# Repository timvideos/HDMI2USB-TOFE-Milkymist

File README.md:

## Milkymist Compatibility - TOFE Expansion board

The [Numato Opsis board](https://numato.com/product/numato-opsis-fpga-based-open-video-platform) is
already very similar to the [Milkymist M1](http://m-labs.hk/m1.html) and
[Mixxeo](http://m-labs.hk/mixxeo.html) devices created by
[M-Labs](http://m-labs.hk/), but lacks the DJ hardware interfaces. This
expansion board adds these missing components.

This board can be ordered from the
[Numato Opsis page on CrowdSupply.com](https://www.crowdsupply.com/numato-lab/opsis).

## Features

This extension board has the following features;

 * [AC‘97 compatible](https://en.wikipedia.org/wiki/AC%2797)
   audio interface with Microphone, Headphones, Line In + Out (on standard
   3.5mm connectors).

 * [RS-422](https://en.wikipedia.org/wiki/RS-422) / [RS-485](https://en.wikipedia.org/wiki/RS-485)
   compatible high speed (10Mbps), full duplex serial port;

    * Compatible with wide range of interfaces including the industry standard
      [DMX512 control protocol](https://en.wikipedia.org/wiki/DMX512).

    * Connected to screw terminal headers, allowing wiring to DB-9, RJ-12,
      XLR-5, XLR-3 or RJ-45 connectors (wiring diagrams provided).

 * [RS-232](https://en.wikipedia.org/wiki/RS-232) full duplex serial port on a
   standard DB-9 connector. Supporting connection to wide range of devices with
   serial ports. (A secondary RS-232 full duplex serial port on a standard
   screw terminal.)

 * [MIDI](https://en.wikipedia.org/wiki/MIDI) In and Out interfaces on screw
   terminals, supporting connection to wide range of musical instruments and
   control devices.

 * [Infrared](https://learn.adafruit.com/ir-sensor/ir-remote-signals)
   transmitter and receiver compatible with manys
   [consumer remote protocols](https://en.wikipedia.org/wiki/Consumer_IR).

 * 4 x Push button Switches,
 * 4 x Indicator LEDs,

 * 2 x [Digilent Pmod™ Compatible](http://www.digilentinc.com/Pmods/licensing.cfm)
   headers to allow usage of existing expansion boards, including boards froms
   [Numato Lab](http://numato.com/fpga-boards/filter/cat/expansion-modules.html?limit=30),
   [Digilent](http://digilentinc.com/pmods),
   [Maxim](https://www.maximintegrated.com/en/design/design-technology/fpga-design-resources/pmod-compatible-plug-in-peripheral-modules.html) ands
   [Analog](https://wiki.analog.com/resources/alliances/xilinx#pmods).

A PDF version of the schematic can be found in the [docs](docs) directory.

## Editing

The design in this repository was made using [KiCad](http://www.kicad-pcb.org/)
version **2013-07-07 BZR 4022**
([the version is Ubuntu Trusty](http://packages.ubuntu.com/trusty/kicad)).

## License

TOFE MilkyMist Compatibility Expansion board by Numato Systems Pvt. Ltd

TOFE MilkyMist Compatibility Expansion board is licensed under a
Creative Commons Attribution-ShareAlike 4.0 International License.

You should have received a copy of the license along with this
work. If not, see <http://creativecommons.org/licenses/by-sa/4.0/>.

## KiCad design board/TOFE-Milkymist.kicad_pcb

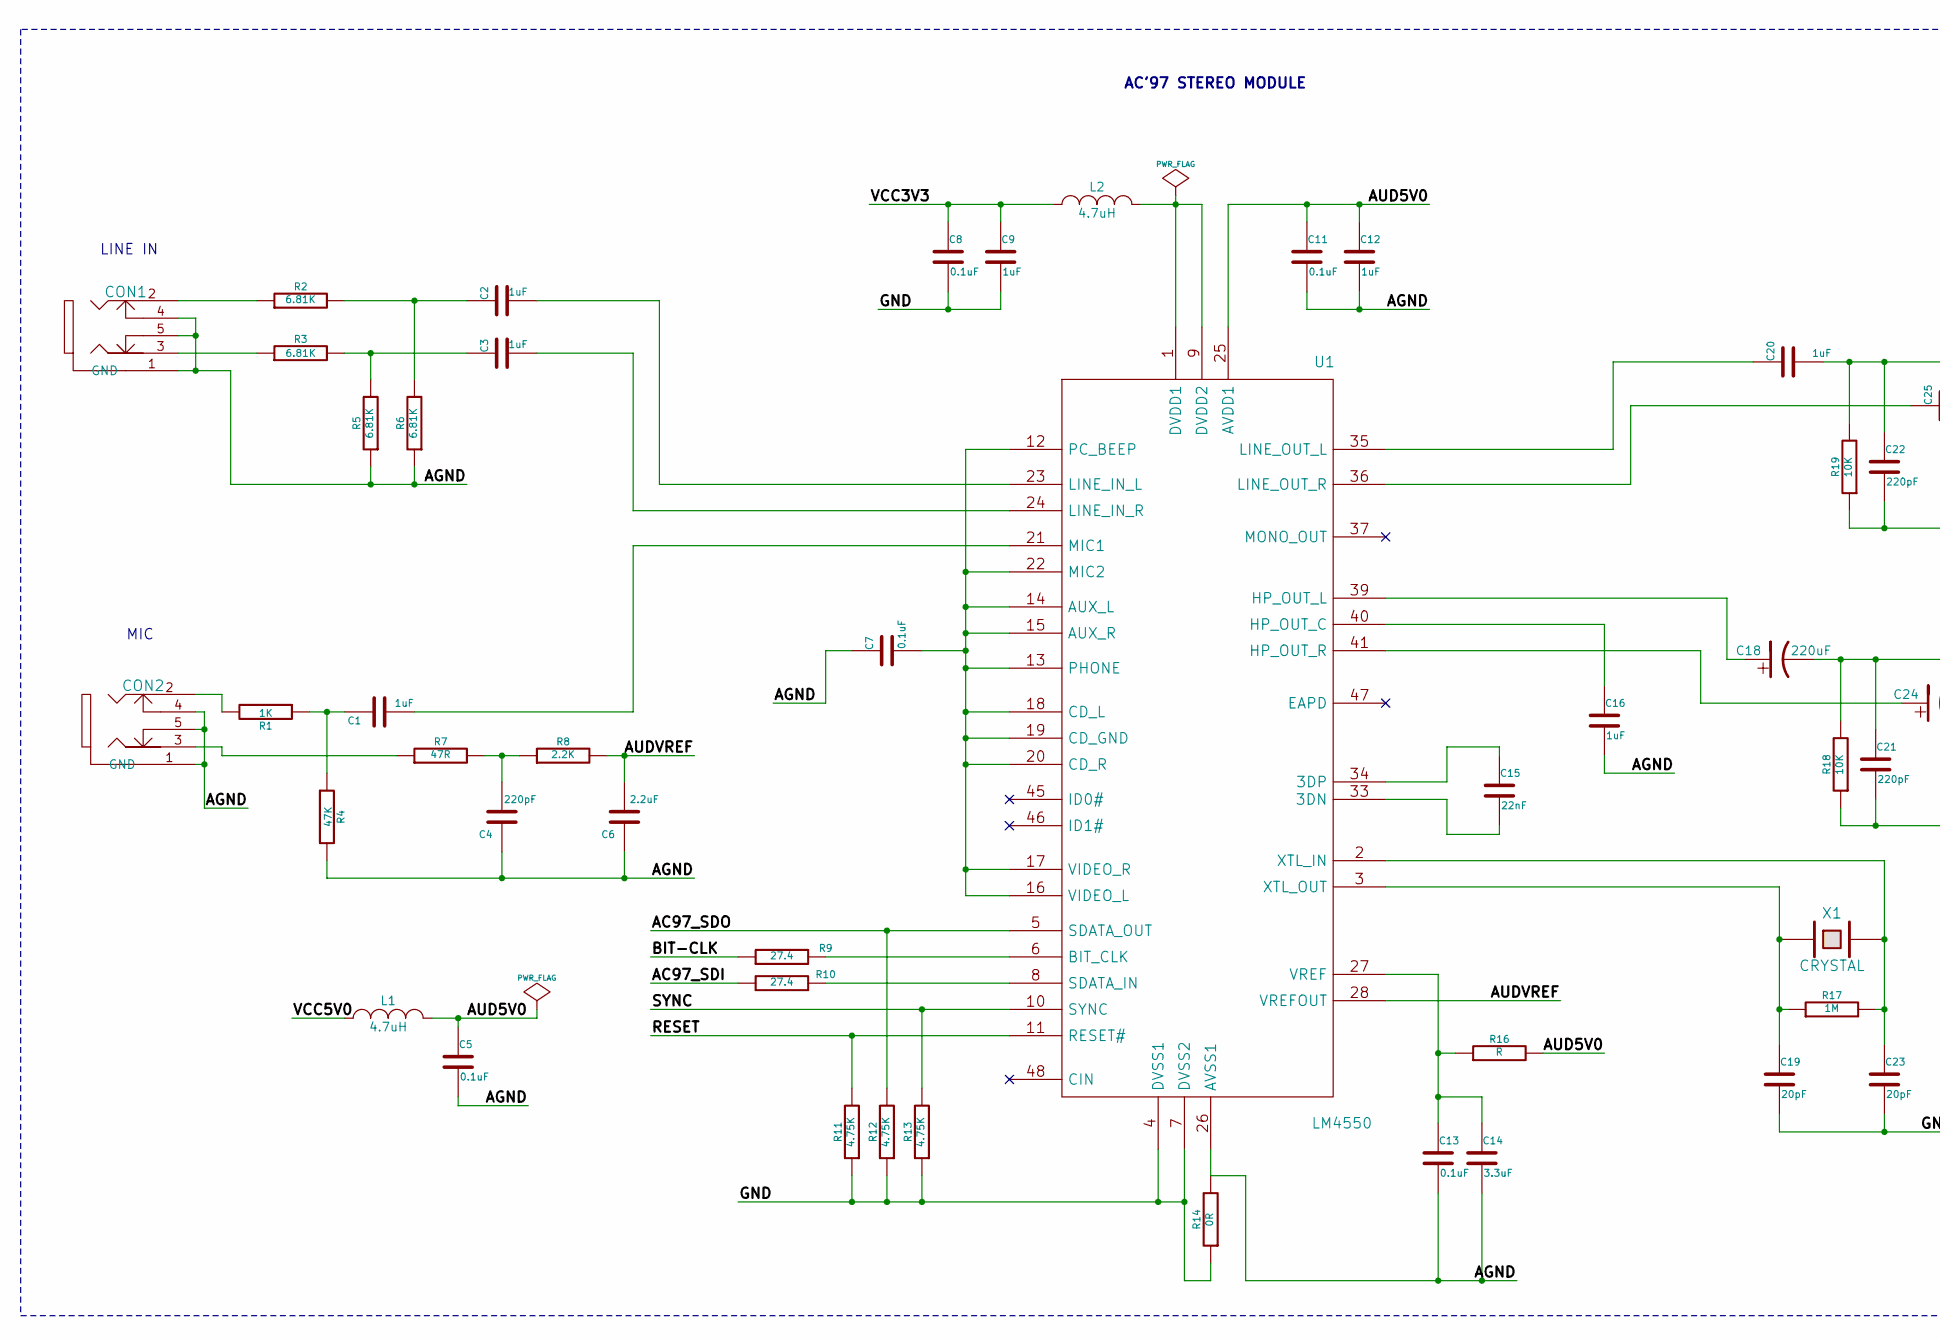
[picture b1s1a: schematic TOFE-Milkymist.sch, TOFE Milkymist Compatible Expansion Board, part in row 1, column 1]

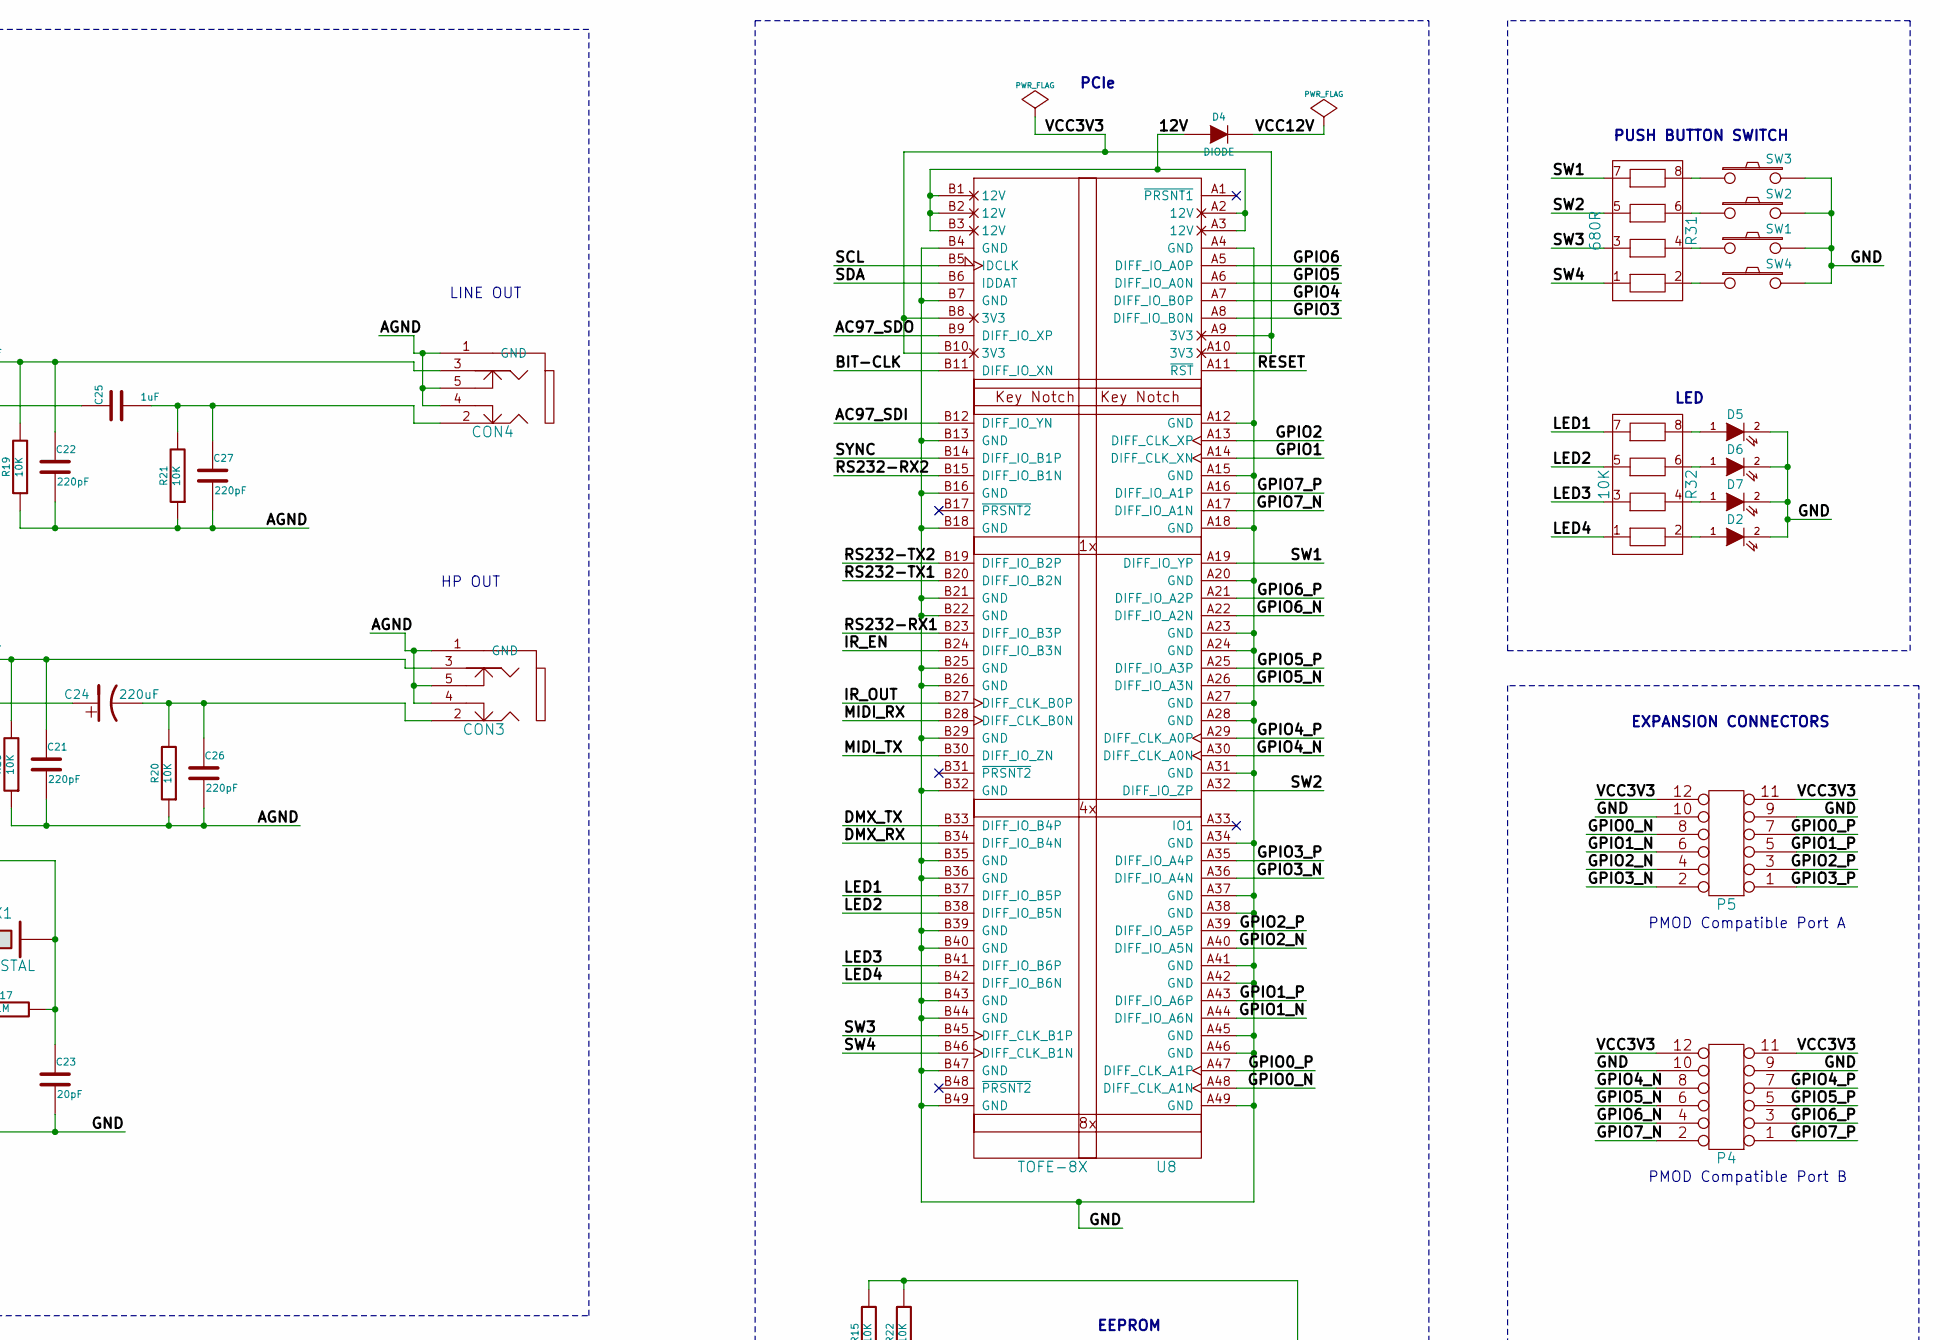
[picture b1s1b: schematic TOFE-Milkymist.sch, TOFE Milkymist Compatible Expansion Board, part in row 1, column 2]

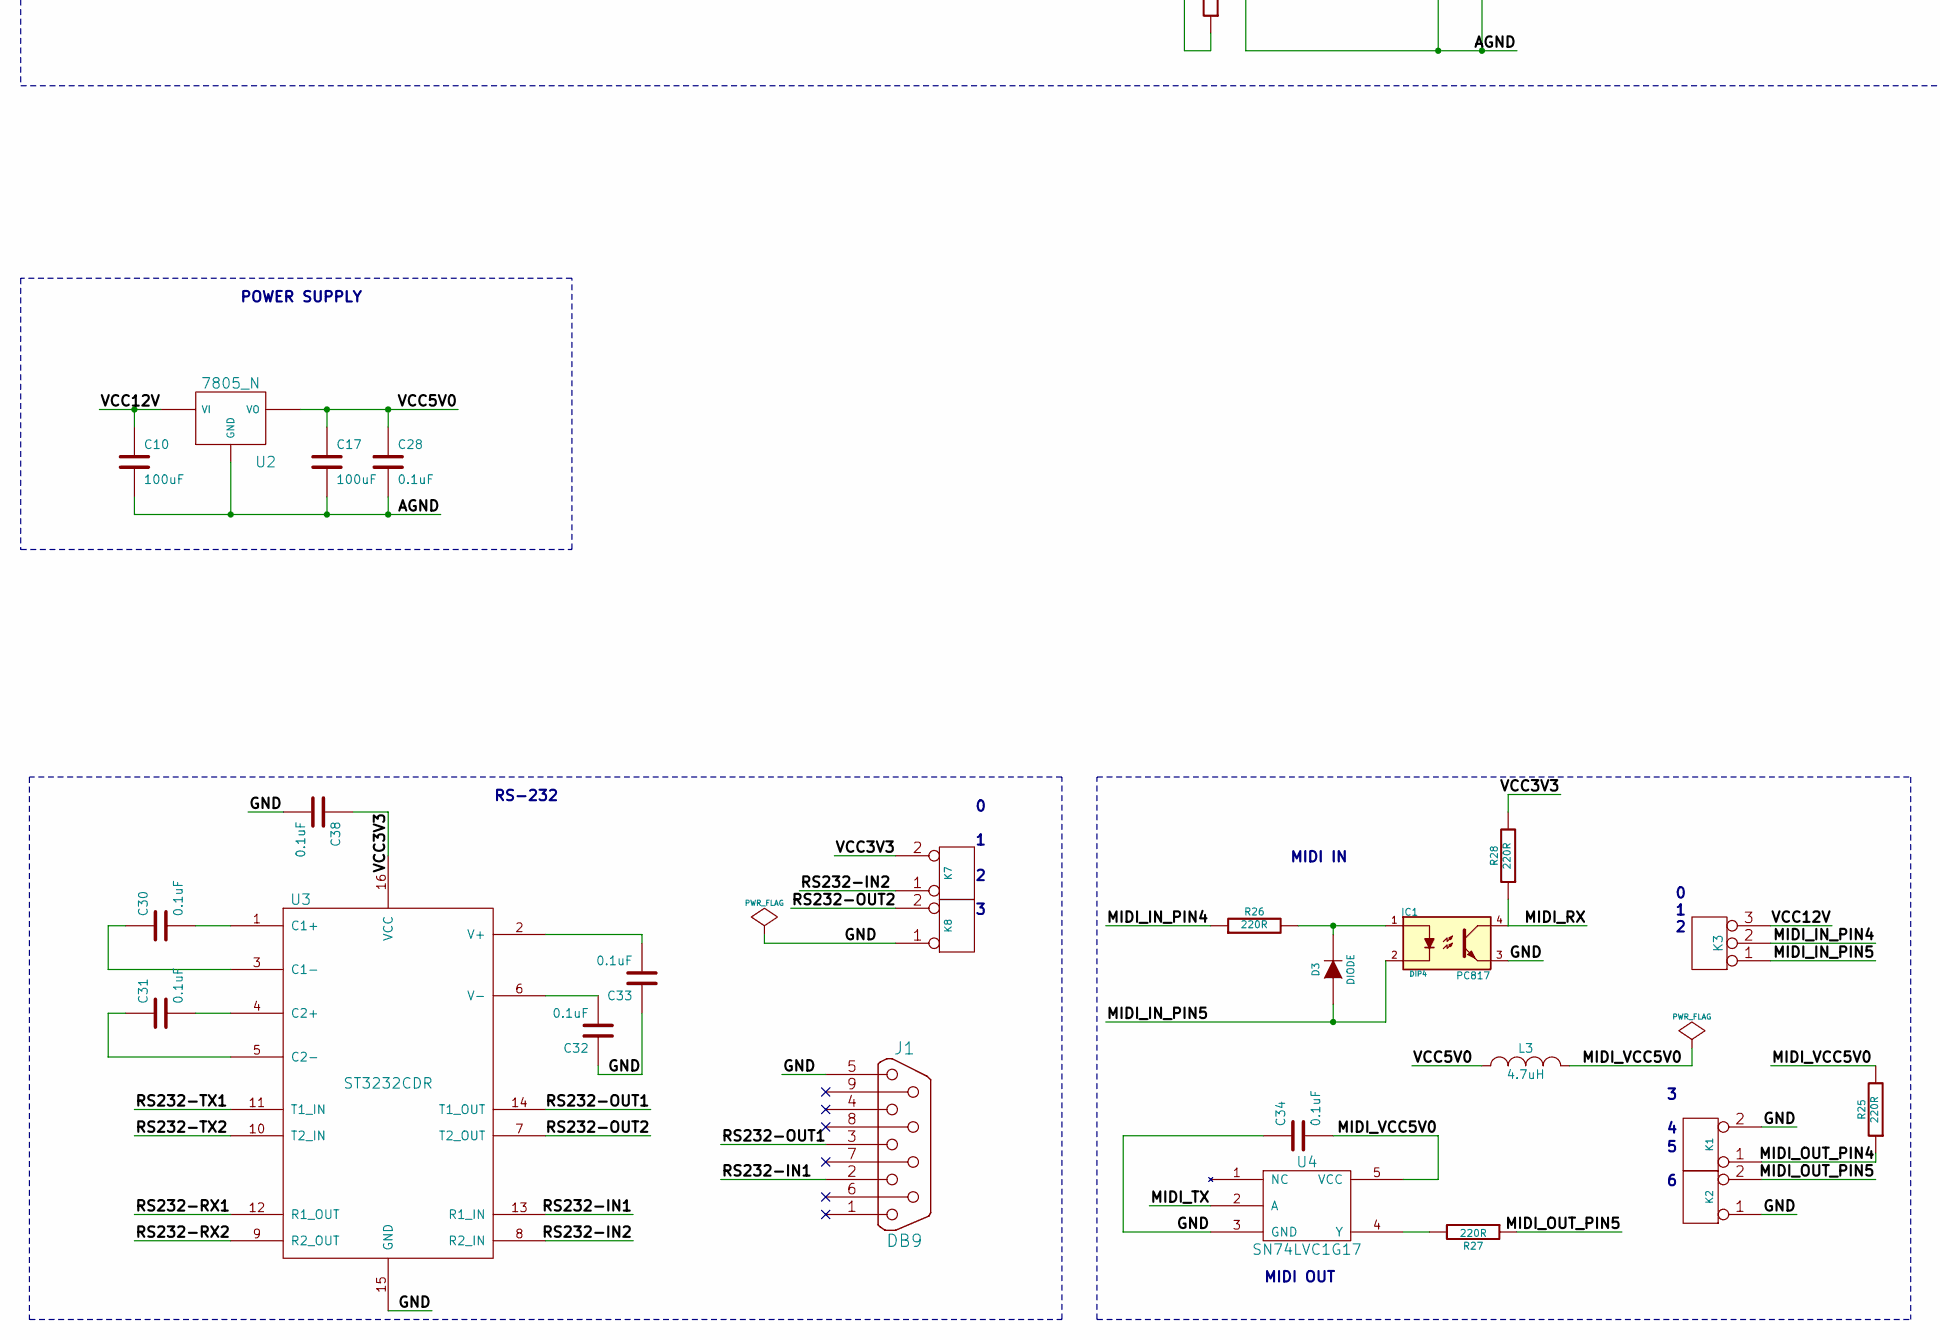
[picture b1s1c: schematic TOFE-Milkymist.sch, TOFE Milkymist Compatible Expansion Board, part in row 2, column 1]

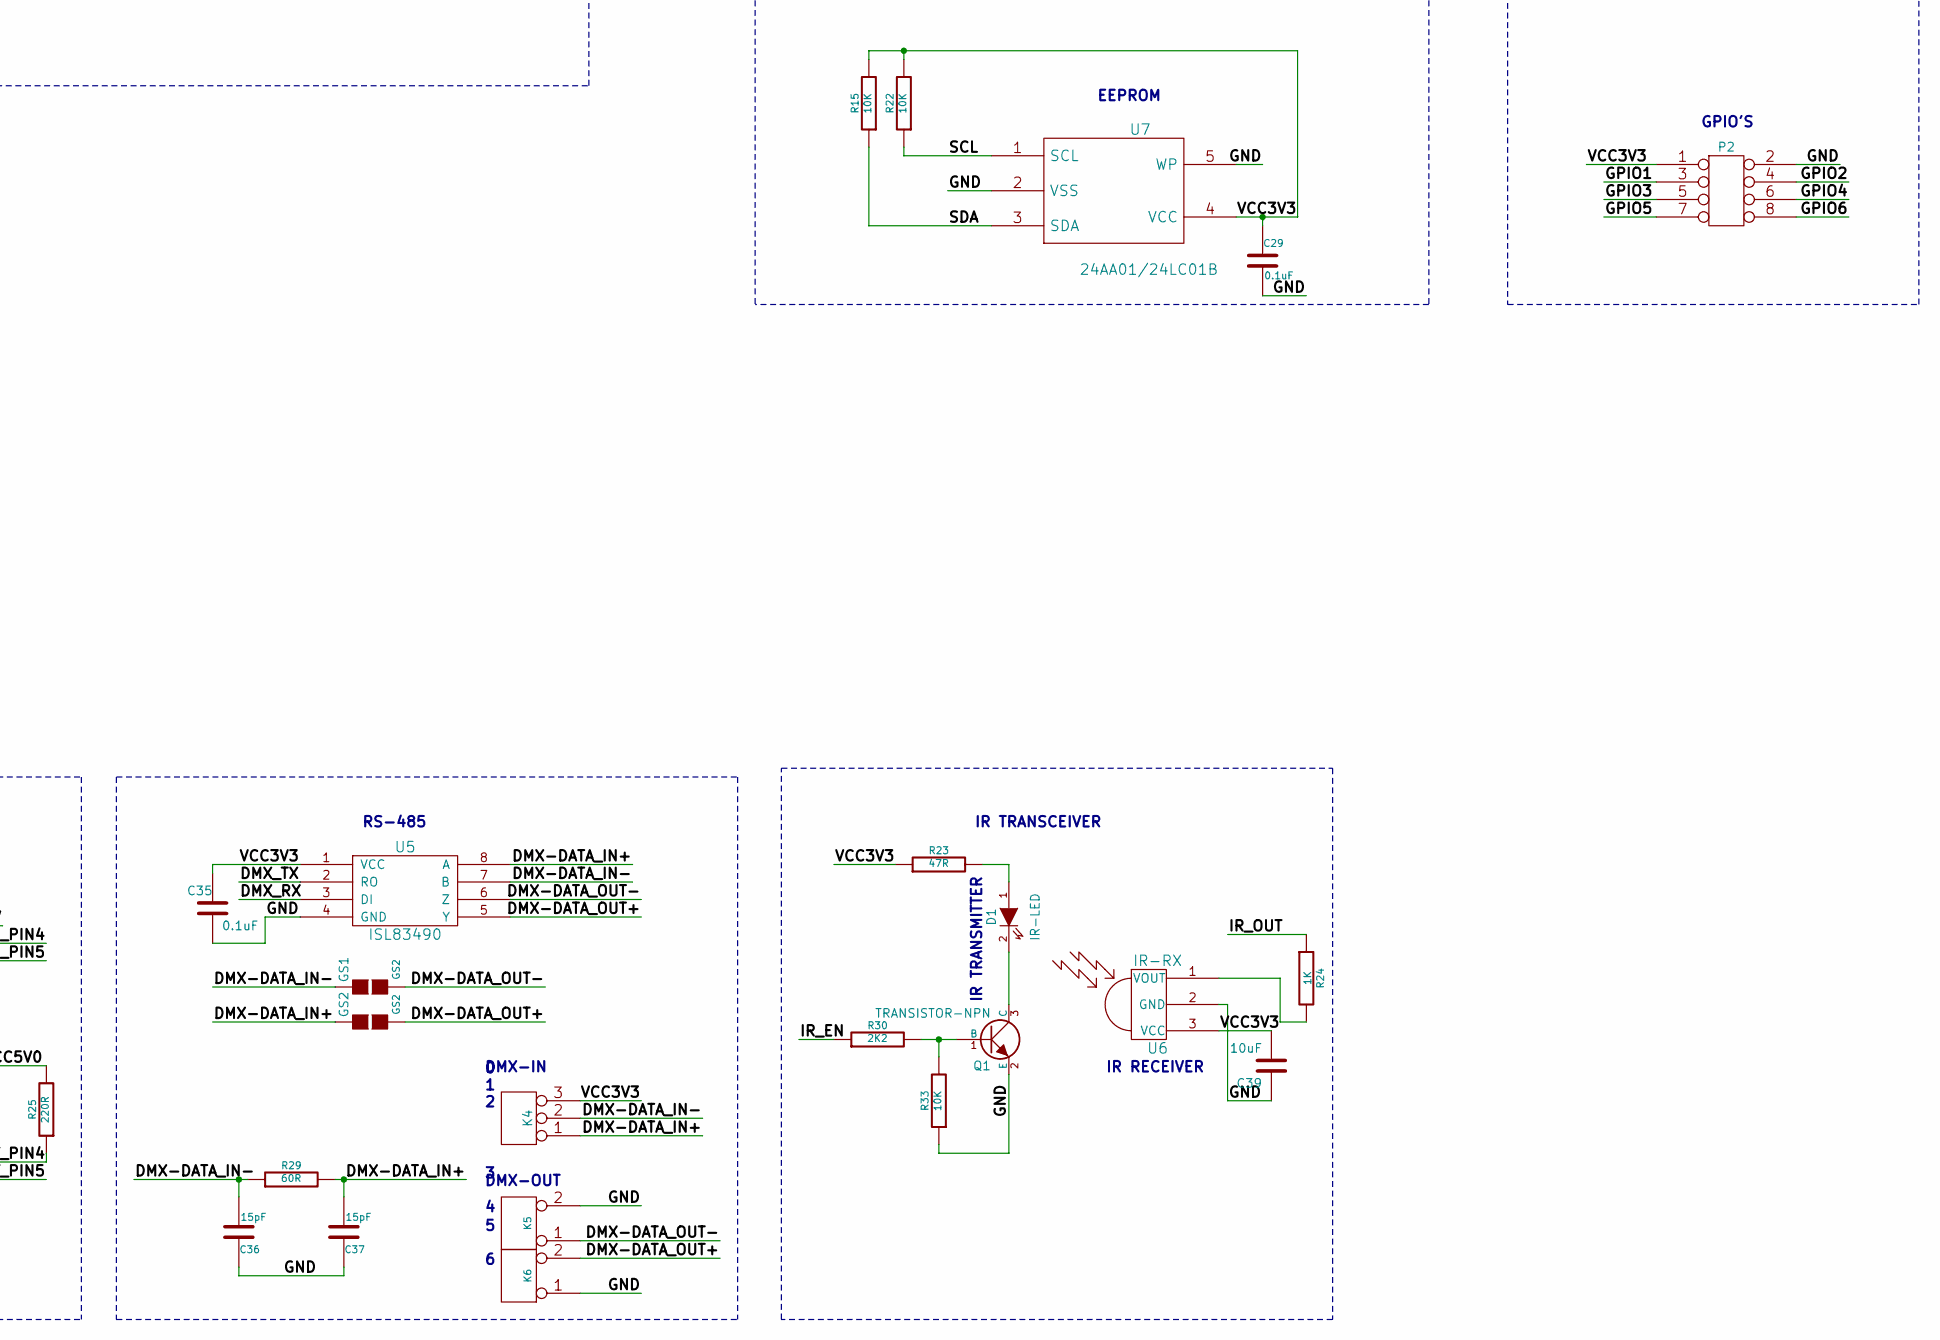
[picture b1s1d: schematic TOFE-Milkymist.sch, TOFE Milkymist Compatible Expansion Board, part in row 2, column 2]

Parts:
C1, C2, C3, C9, C12, C16, C20, C25: 1uF
C4, C21, C22, C26, C27: 220pF
C5, C7, C8, C11, C13, C28, C29, C30, C31, C32, C33, C34, C35, C38: 0.1uF
C6: 2.2uF
C10, C17: 100uF
C14: 3.3uF
C15: 22nF
C18, C24: 220uF
C19, C23: 20pF
C36, C37: 15pF
C39: 10uF
CON1, CON2, CON3, CON4: AUDIO_JACK_3535NG
D1: IR-LED
D2, D5, D6, D7: LED
D3, D4: DIODE
GS1, GS2: GS2
IC1: PC817; DIP4
J1: DB9
K1, K2, K5, K6, K7, K8: CONN_2
K3, K4: CONN_3
L1, L2, L3: 4.7uH
P2: CONN_4X2
P4, P5: CONN_6X2
Q1: TRANSISTOR-NPN
R1, R24: 1K
R2, R3, R5, R6: 6.81K
R4: 47K
R7, R23: 47R
R8: 2.2K
R9, R10: 27.4
R11, R12, R13: 4.75K
R14: 0R
R15, R18, R19, R20, R21, R22, R32, R33: 10K
R16: R
R17: 1M
R25, R26, R27, R28: 220R
R29: 60R
R30: 2K2
R31: 680R
SW1, SW2, SW3, SW4: SW_PUSH
U1: LM4550
U2: 7805_N
U3: ST3232CDR
U4: SN74LVC1G17
U5: ISL83490
U6: IR-RX
U7: 24AA01/24LC01B
U8: TOFE-8X
X1: CRYSTAL

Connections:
/12V: D4.1 (A), U8.A2 (12V), U8.A3 (12V), U8.B1 (12V), U8.B2 (12V), U8.B3 (12V)
/AC97_SDI: R10.1, U8.B12 (DIFF_IO_YN)
/AC97_SDO: R12.2, U1.5 (SDATA_OUT), U8.B9 (DIFF_IO_XP)
/AGND: C4.1, C5.2, C6.1, C7.1, C10.2, C11.2, C12.2, C13.2, C14.2, C16.2, C17.2, C21.2, C22.2, C26.2, C27.2, C28.2, CON1.1 (GND), CON1.4, CON1.5, CON2.1 (GND), CON2.4, CON2.5, CON3.1 (GND), CON3.4, CON3.5, CON4.1 (GND), CON4.4, CON4.5, R4.2, R5.1, R6.1, R14.2, R18.1, R19.1, R20.1, R21.1, U1.26 (AVSS1), U2.2 (GND)
/AUD5V0: C5.1, C11.1, C12.1, L1.2, R16.2, U1.25 (AVDD1)
/AUDVREF: C6.2, R8.2, U1.28 (VREFOUT)
/BIT-CLK: R9.1, U8.B11 (DIFF_IO_XN)
/DMX-DATA_IN+: C37.2, GS2.1 (G1), K4.1, R29.2, U5.8 (A)
/DMX-DATA_IN-: C36.2, GS1.1 (G1), K4.2 (PM), R29.1, U5.7 (B)
/DMX-DATA_OUT+: GS2.2 (G2), K6.2 (PM), U5.5 (Y)
/DMX-DATA_OUT-: GS1.2 (G2), K5.1, U5.6 (Z)
/DMX_RX: U5.3 (DI), U8.B34 (DIFF_IO_B4N)
/DMX_TX: U5.2 (RO), U8.B33 (DIFF_IO_B4P)
/GND: C8.2, C9.2, C19.2, C23.2, C29.2, C32.1, C33.1, C34.1, C35.2, C36.1, C37.1, C38.2, C39.1, D2.2 (K), D5.2 (K), D6.2 (K), D7.2 (K), IC1.3, J1.5, K1.2 (PM), K2.1, K5.2 (PM), K6.1, K8.1, P2.2, P4.9, P4.10, P5.9, P5.10, Q1.2 (E), R11.1, R12.1, R13.1, R14.1, R33.1, SW1.2, SW2.2, SW3.2, SW4.2, U1.4 (DVSS1), U1.7 (DVSS2), U3.15 (GND), U4.3 (GND), U5.4 (GND), U6.2 (GND), U7.2 (VSS), U7.5 (WP), U8.A4 (GND), U8.A12 (GND), U8.A15 (GND), U8.A18 (GND), U8.A20 (GND), U8.A23 (GND), U8.A24 (GND), U8.A27 (GND), U8.A28 (GND), U8.A31 (GND), U8.A34 (GND), U8.A37 (GND), U8.A38 (GND), U8.A41 (GND), U8.A42 (GND), U8.A45 (GND), U8.A46 (GND), U8.A49 (GND), U8.B4 (GND), U8.B7 (GND), U8.B13 (GND), U8.B16 (GND), U8.B18 (GND), U8.B21 (GND), U8.B22 (GND), U8.B25 (GND), U8.B26 (GND), U8.B29 (GND), U8.B32 (GND), U8.B35 (GND), U8.B36 (GND), U8.B39 (GND), U8.B40 (GND), U8.B43 (GND), U8.B44 (GND), U8.B47 (GND), U8.B49 (GND)
/GPIO0_N: P5.8, U8.A48 (DIFF_CLK_A1N)
/GPIO0_P: P5.7, U8.A47 (DIFF_CLK_A1P)
/GPIO1: P2.3, U8.A14 (DIFF_CLK_XN)
/GPIO1_N: P5.6, U8.A44 (DIFF_IO_A6N)
/GPIO1_P: P5.5, U8.A43 (DIFF_IO_A6P)
/GPIO2: P2.4, U8.A13 (DIFF_CLK_XP)
/GPIO2_N: P5.4, U8.A40 (DIFF_IO_A5N)
/GPIO2_P: P5.3, U8.A39 (DIFF_IO_A5P)
/GPIO3: P2.5, U8.A8 (DIFF_IO_B0N)
/GPIO3_N: P5.2, U8.A36 (DIFF_IO_A4N)
/GPIO3_P: P5.1, U8.A35 (DIFF_IO_A4P)
/GPIO4: P2.6, U8.A7 (DIFF_IO_B0P)
/GPIO4_N: P4.8, U8.A30 (DIFF_CLK_A0N)
/GPIO4_P: P4.7, U8.A29 (DIFF_CLK_A0P)
/GPIO5: P2.7, U8.A6 (DIFF_IO_A0N)
/GPIO5_N: P4.6, U8.A26 (DIFF_IO_A3N)
/GPIO5_P: P4.5, U8.A25 (DIFF_IO_A3P)
/GPIO6: P2.8, U8.A5 (DIFF_IO_A0P)
/GPIO6_N: P4.4, U8.A22 (DIFF_IO_A2N)
/GPIO6_P: P4.3, U8.A21 (DIFF_IO_A2P)
/GPIO7_N: P4.2, U8.A17 (DIFF_IO_A1N)
/GPIO7_P: P4.1, U8.A16 (DIFF_IO_A1P)
/IR_EN: R30.1, U8.B24 (DIFF_IO_B3N)
/IR_OUT: R24.1, U8.B27 (DIFF_CLK_B0P)
/LED1: R32.7, U8.B37 (DIFF_IO_B5P)
/LED2: R32.5, U8.B38 (DIFF_IO_B5N)
/LED3: R32.3, U8.B41 (DIFF_IO_B6P)
/LED4: R32.1, U8.B42 (DIFF_IO_B6N)
/MIDI_IN_PIN4: K3.2 (PM), R26.1
/MIDI_IN_PIN5: D3.1 (A), IC1.2, K3.1
/MIDI_OUT_PIN4: K1.1, R25.1
/MIDI_OUT_PIN5: K2.2 (PM), R27.1
/MIDI_RX: IC1.4, R28.1, U8.B28 (DIFF_CLK_B0N)
/MIDI_TX: U4.2 (A), U8.B30 (DIFF_IO_ZN)
/MIDI_VCC5V0: C34.2, L3.2, R25.2, U4.5 (VCC)
/RESET: R11.2, U1.11 (RESET#), U8.A11 (~RST)
/RS232-IN1: J1.2, U3.13 (R1_IN)
/RS232-IN2: K7.1, U3.8 (R2_IN)
/RS232-OUT1: J1.3, U3.14 (T1_OUT)
/RS232-OUT2: K8.2 (PM), U3.7 (T2_OUT)
/RS232-RX1: U3.12 (R1_OUT), U8.B23 (DIFF_IO_B3P)
/RS232-RX2: U3.9 (R2_OUT), U8.B15 (DIFF_IO_B1N)
/RS232-TX1: U3.11 (T1_IN), U8.B20 (DIFF_IO_B2N)
/RS232-TX2: U3.10 (T2_IN), U8.B19 (DIFF_IO_B2P)
/SCL: R22.1, U7.1 (SCL), U8.B5 (IDCLK)
/SDA: R15.1, U7.3 (SDA), U8.B6 (IDDAT)
/SW1: R31.7, U8.A19 (DIFF_IO_YP)
/SW2: R31.5, U8.A32 (DIFF_IO_ZP)
/SW3: R31.3, U8.B45 (DIFF_CLK_B1P)
/SW4: R31.1, U8.B46 (DIFF_CLK_B1N)
/SYNC: R13.2, U1.10 (SYNC), U8.B14 (DIFF_IO_B1P)
/VCC3V3: C8.1, C9.1, C29.1, C35.1, C38.1, C39.2, K4.3, K7.2 (PM), L2.1, P2.1, P4.11, P4.12, P5.11, P5.12, R15.2, R22.2, R23.1, R28.2, U3.16 (VCC), U5.1 (VCC), U6.3 (VCC), U7.4 (VCC), U8.A9 (3V3), U8.A10 (3V3), U8.B8 (3V3), U8.B10 (3V3)
/VCC5V0: C17.1, C28.1, L1.1, L3.1, U2.3 (VO)
/VCC12V: C10.1, D4.2 (K), K3.3, U2.1 (VI)
unnamed: CON2.3, R7.1
unnamed: CON2.2, R1.2
unnamed: C3.2, U1.24 (LINE_IN_R)
unnamed: C2.2, U1.23 (LINE_IN_L)
unnamed: C13.1, C14.1, R16.1, U1.27 (VREF)
unnamed: C18.2, C21.1, CON3.3, R18.2
unnamed: C24.1, U1.41 (HP_OUT_R)
unnamed: C15.2, U1.33 (3DN)
unnamed: C15.1, U1.34 (3DP)
unnamed: R10.2, U1.8 (SDATA_IN)
unnamed: R9.2, U1.6 (BIT_CLK)
unnamed: C1.1, R1.1, R4.1
unnamed: C20.1, U1.35 (LINE_OUT_L)
unnamed: C25.1, U1.36 (LINE_OUT_R)
unnamed: C1.2, U1.21 (MIC1)
unnamed: C4.2, R7.2, R8.1
unnamed: C16.1, U1.40 (HP_OUT_C)
unnamed: C24.2, C26.1, CON3.2, R20.2
unnamed: C25.2, C27.1, CON4.2, R21.2
unnamed: C20.2, C22.1, CON4.3, R19.2
unnamed: C18.1, U1.39 (HP_OUT_L)
unnamed: R27.2, U4.4 (Y)
unnamed: R31.2, SW4.1
unnamed: R24.2, U6.1 (VOUT)
unnamed: D1.2 (K), Q1.3 (C)
unnamed: Q1.1 (B), R30.2, R33.2
unnamed: D1.1 (A), R23.2
unnamed: D7.1 (A), R32.4
unnamed: D6.1 (A), R32.6
unnamed: D5.1 (A), R32.8
unnamed: R31.4, SW1.1
unnamed: R31.6, SW2.1
unnamed: R31.8, SW3.1
unnamed: C30.2, U3.1 (C1+)
unnamed: C33.2, U3.2 (V+)
unnamed: C31.1, U3.5 (C2-)
unnamed: C31.2, U3.4 (C2+)
unnamed: C30.1, U3.3 (C1-)
unnamed: D2.1 (A), R32.2
unnamed: C32.2, U3.6 (V-)
unnamed: D3.2 (K), IC1.1, R26.2
unnamed: CON1.3, R3.1
unnamed: CON1.2, R2.1
unnamed: C2.1, R2.2, R6.2
unnamed: C7.2, U1.12 (PC_BEEP), U1.13 (PHONE), U1.14 (AUX_L), U1.15 (AUX_R), U1.16 (VIDEO_L), U1.17 (VIDEO_R), U1.18 (CD_L), U1.19 (CD_GND), U1.20 (CD_R), U1.22 (MIC2)
unnamed: C23.1, R17.2, U1.2 (XTL_IN), X1.2
unnamed: C19.1, R17.1, U1.3 (XTL_OUT), X1.1
unnamed: L2.2, U1.1 (DVDD1), U1.9 (DVDD2)
unnamed: C3.1, R3.2, R5.2

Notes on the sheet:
LINE IN
LINE OUT
HP OUT
MIC
PUSH BUTTON SWITCH
LED
PCIe
EEPROM
MIDI IN
MIDI OUT
EXPANSION CONNECTORS
RS-485
POWER SUPPLY
AC'97 STEREO MODULE
RS-232
IR TRANSCEIVER
0 1 2
3 4
GPIO'S
DMX-IN
DMX-OUT
IR TRANSMITTER
IR RECEIVER
0 1
2 3
5 6
PMOD Compatible Port A
PMOD Compatible Port B

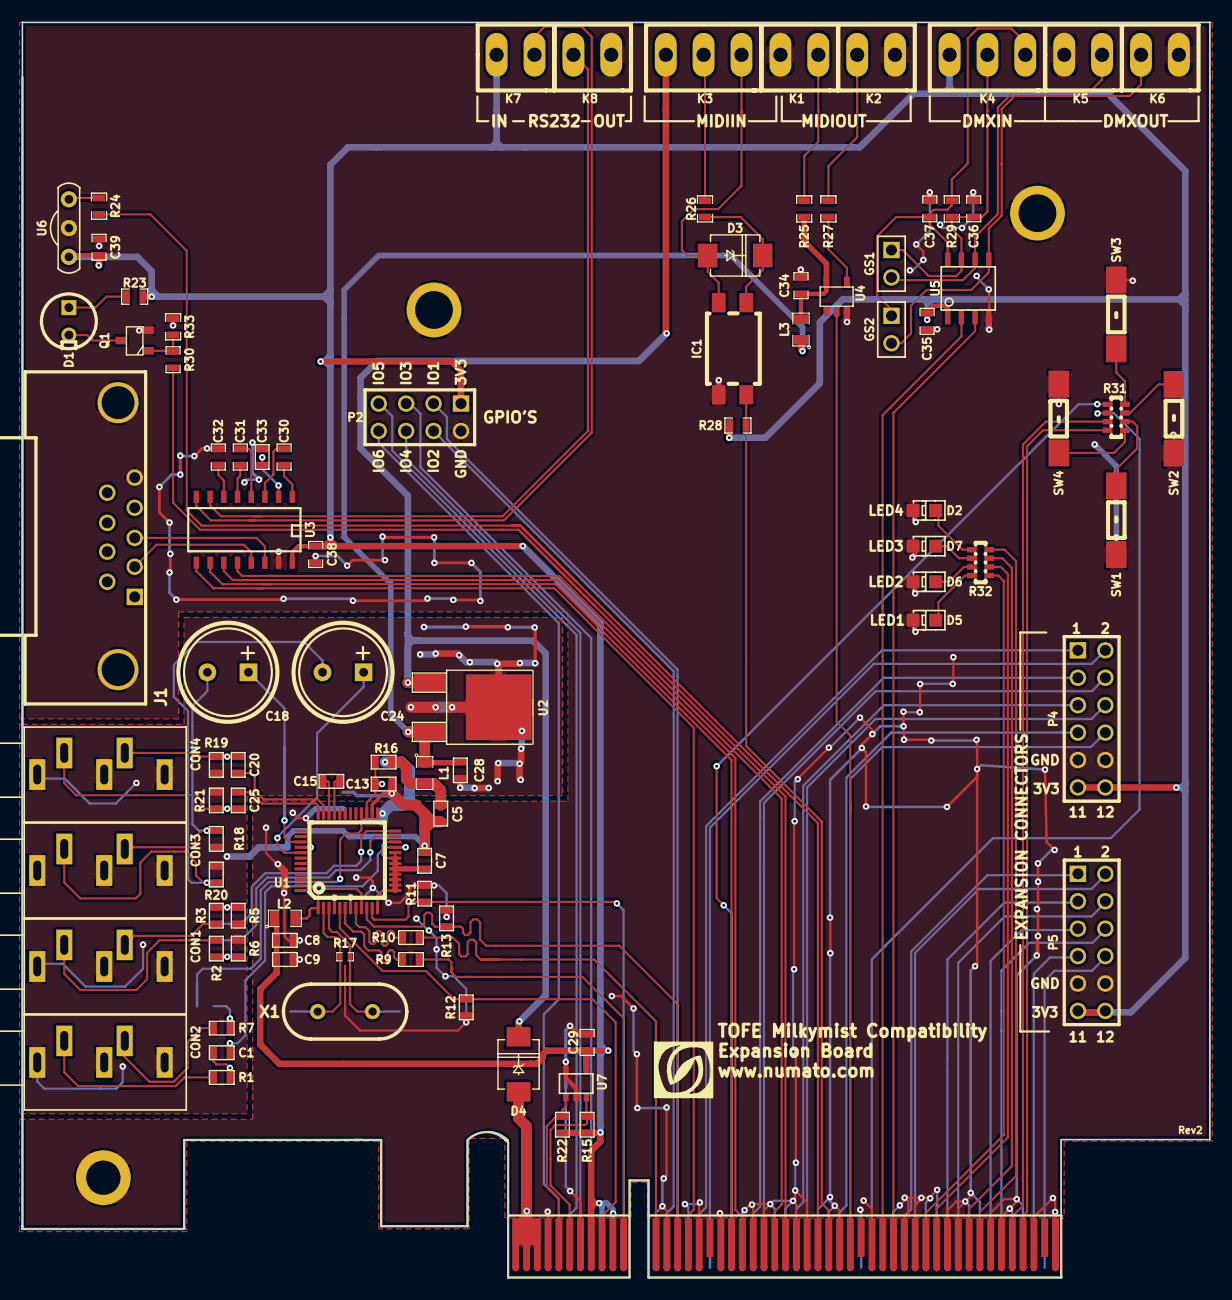
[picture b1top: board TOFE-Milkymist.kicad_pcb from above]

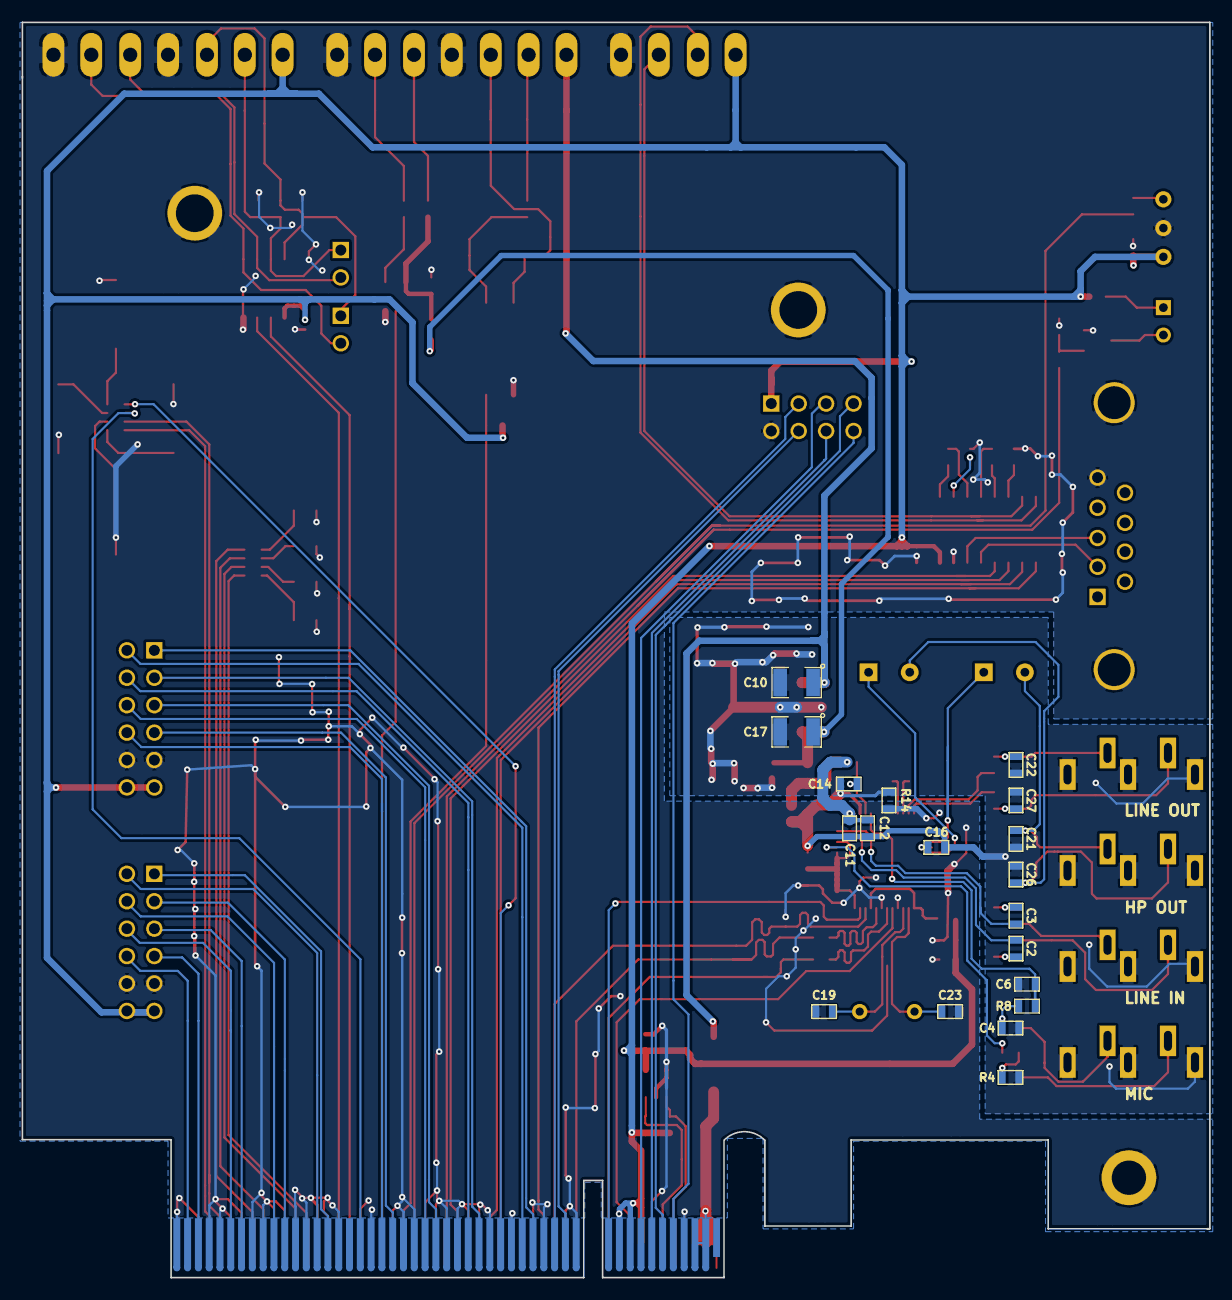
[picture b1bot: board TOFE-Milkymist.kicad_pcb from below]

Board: 2 copper layers, 110.0 x 116.3 mm, 115 parts (19 on the bottom side), 117 nets.

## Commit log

2015-11-03 Changes on 03-11-15
2015-11-03 changes on Mounting holes arrangement
2015-12-02 Mechanical hole changes
2015-12-22 Creating TOFE-Milkymist!
2015-12-22 Updating README and LICENSE file.
2015-12-22 Initial version from on 2015-11-03
2015-12-22 Changing mounting holes arrangement.
2015-12-22 More changes to mechanical holes.
2015-12-22 Slight fix to README file.
2015-12-22 Fixing part reference.
2015-12-22 Fixing switch alignment and adding extra comments.
2015-12-22 Slight fixes to README.
2015-12-22 Updated version sent to production.
2015-12-22 Gerber's sent to production.
2016-01-11 Improving comments.
2016-01-11 Adding PDF of schematic.
2016-05-26 Adding images of the board.
2016-05-26 Adding a features heading to the README.
2018-04-27 Link to current Opsis supplier page

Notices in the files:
board/TOFE-Milkymist.kicad_pcb:
License: CC BY-SA
